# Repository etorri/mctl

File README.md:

# Objective

The purpose of this pile of rubbish is to build a controller between
Raspberry Pi UART (or SPI) and Pololu 708 (Dual VNH2SP30 Motor Driver
Carrier MD03A) with two DC gear motors (FIT0277).

The controller is based on msp430G2553 (20-pin) because I have several of them.
Besides that, it has nice peripherals to implement

- wall clock with timer A0 to measure time intervals (encoders)
- sufficiently fast two channel PWM (10-20KHz) with timers A1
- UART,SPI or I2C clock
- interrupts from the rotary encoders of the motors.
- just enough IO ports

The code is designed for this particular application. It may have
useful components and "Notes to Self" comments that somebody finds
useful.

# Control?

The Pi tells the controller to

- Initialize
- Break
- Prepare to run
- Run with given PWM values
- Error recovery
- Sleep

The controller reports back to Pi

- state of the controller
- position and speed (and current) of the two motors
- errors reported by the driver chip

# Pins wasted

The following pins of the msp430G2553 are misused for the purpose
(see the eagle files)

Left side, top to down

| Pin# | Port | Function | Description      |
|------+------+----------+------------------|
|    1 | DVCC | +3.3v    | Electrons exit   |
|    2 | P1.0 | IO       | out: L ENA       |
|    3 | P1.1 | UART RX  | data from Pi     |
|    4 | P1.2 | UART TX  | data to Pi       |
|    5 | P1.3 | IO       | in : L DIAG      |
|    6 | P1.4 | IO       | in : L Encoder B |
|    7 | P1.5 | IO       | in : L Encoder A |
|    8 | P2.0 | IO       | out: L INB       |
|    9 | P2.1 | TA1.1    | out: L PWM       |
|   10 | P2.2 | IO       | out: L INA       |

Right Side, top to down

| Pin# | Port | Function | Description       |
|------+------+----------+-------------------|
|   20 | DVSS | +0v      | Electrons enter   |
|   19 | P2.6 | IO       | out: R ENA        |
|   18 | P2.7 | IO       | in : R DIAG       |
|   17 | x    | TEST     | Programmer        |
|   16 | x    | RESET    | Programmer        |
|   15 | P1.7 | IO       | in :  R Encoder B |
|   14 | P1.6 | IO       | in :  R Encoder A |
|   13 | P2.5 | IO       | out: R INB        |
|   12 | P2.4 | TA1.2    | out: R PWM        |
|   11 | P2.3 | IO       | out: R INA        |

The motor driver also provides two Current Sense (CS) analog outputs
that tell how many amps go through a motor.

# CPU settings

Low power operation (at which the msp430 is also good at) is not
within the scope. It runs full speed 16MHz from the DCO oscillator.

# Motor control signals to the driver

The controller will handle the confusion that left motor will turn
Clockwise (CW) and right CounterClockWise (CCW) when going forward. 
The Power settings received from the Pi are signed integers bounded
by the timer A1 TA1CCR0 count (PWM frequency).
Negative number means going backwards and positive forwards.

Three states of INA and INB motor driver pins are used 

| State         | L INA | L INB | R INA | R INB |
|---------------|-------|-------|-------|-------|
| Power(x) >= 0 |     1 |     0 |     0 |     1 |
| Power(x) < 0  |     0 |     1 |     1 |     0 |
| Braking       |     0 |     0 |     0 |     0 |

Braking state means shorting both motors to ground. With the 51:1 gears
this shouldn't really be necessary.

The PWM has 10KHz frequency and motor driver documentation says max 20KHz.
DCO clock 16MHZ with

The driver operates at 5v and high level signal is 3.27v which is
uncomfortably close to the 3.3v of msp430 so level converters are needed.

The INA, INB pins in MSP need to be in the same port to be able to change
them simultaneously. Otherwise the motor might be in braking mode for
a short period. Documentation mentions 

Example:

~~~~
#define LINA BIT4 
#define LINB BIT3
P2OUT = (P2OUT&~LINB)|LINA; // Left motor forward in one op
P2OUT = (P2OUT&~LINA)|LINB; // Left motor backward
P2OUT &= ~(LINA|LINB);      // Left Brake
~~~~

# Encoder signals from the motors

*Speculation based on the vague docs, need to be verified with the hardware*

Hall effect quadrature encoder will give 13 interrupts per 
one motor rotation on the A input. The gearbox is 51:1 which makes it
663 interrupts per one rotation of the wheel.

At 16MHz it seems that by initial measurements
this MSP430 chip can handle 160K interrupts per second 
or 80K interrupts/s per wheel with highly unoptimized C code ISRs.
So the ISR is bounded with wheel speeds of 120r/s. The motor+gear documentation
mentions ~3 r/s for top speed which makes me believe this should not be a problem.

The accuracy looks pretty good when measured with the 2MHz wall clock
timer implemented with T0. Connecting the PWM output to encoder A input
gives variation of one step (0.5 microseconds).

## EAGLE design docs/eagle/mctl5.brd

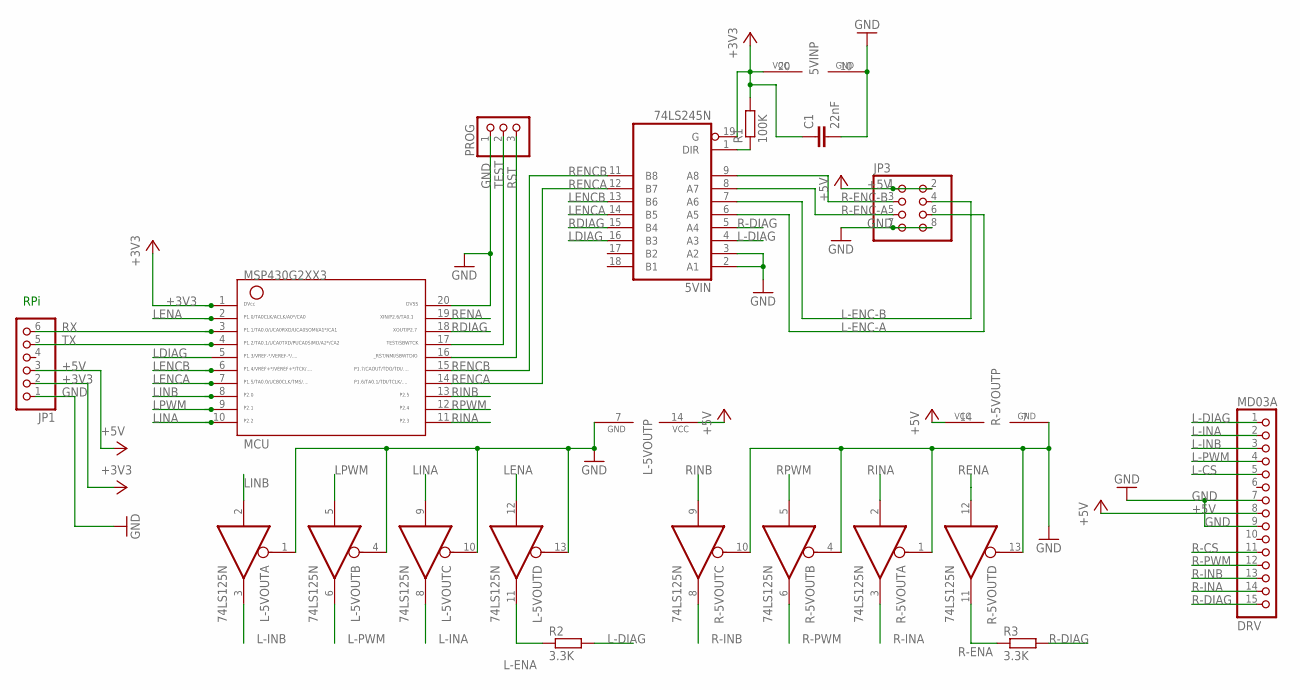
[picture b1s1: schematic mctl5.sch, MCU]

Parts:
5VIN: 74LS245N; DIL20
C1: 22nF; C025-024X044
JP1: PINHD-1X6; 1X06
JP3: PINHD-2X4; 2X04
L-5VOUT: 74LS125N; DIL14
MCU: G2XX3---N20; N20
MD03A: DRV; 1X15-CB
PROG: PINHD-1X3; 1X03
R1: 100K; 0204/7
R2, R3: 3.3K; 0204/7
R-5VOUT: 74LS125N; DIL14

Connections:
+3V3: 5VIN.19 (G), 5VIN.20 (VCC), C1.1, JP1.2, MCU.1, R1.2
+5V: JP1.3, JP3.1, JP3.2, L-5VOUT.14 (VCC), MD03A.8, R-5VOUT.14 (VCC)
GND: 5VIN.2 (A1), 5VIN.3 (A2), 5VIN.10 (GND), C1.2, JP1.1, JP3.7, JP3.8, L-5VOUT.1 (OE), L-5VOUT.4 (OE), L-5VOUT.7 (GND), L-5VOUT.10 (OE), L-5VOUT.13 (OE), MCU.20, MD03A.7, MD03A.9, PROG.1, R-5VOUT.1 (OE), R-5VOUT.4 (OE), R-5VOUT.7 (GND), R-5VOUT.10 (OE), R-5VOUT.13 (OE)
L-CS: MD03A.5
L-DIAG: 5VIN.4 (A3), MD03A.1, R2.2
L-ENA: L-5VOUT.11 (O), R2.1
L-ENC-A: 5VIN.6 (A5), JP3.6
L-ENC-B: 5VIN.7 (A6), JP3.4
L-INA: L-5VOUT.8 (O), MD03A.2
L-INB: L-5VOUT.3 (O), MD03A.3
L-PWM: L-5VOUT.6 (O), MD03A.4
LDIAG: 5VIN.16 (B3), MCU.5
LENA: L-5VOUT.12 (I), MCU.2
LENCA: 5VIN.14 (B5), MCU.7
LENCB: 5VIN.13 (B6), MCU.6
LINA: L-5VOUT.9 (I), MCU.10
LINB: L-5VOUT.2 (I), MCU.8
LPWM: L-5VOUT.5 (I), MCU.9
unnamed: 5VIN.1 (DIR), R1.1
R-CS: MD03A.11
R-DIAG: 5VIN.5 (A4), MD03A.15, R3.2
R-ENA: R3.1, R-5VOUT.11 (O)
R-ENC-A: 5VIN.8 (A7), JP3.5
R-ENC-B: 5VIN.9 (A8), JP3.3
R-INA: MD03A.14, R-5VOUT.3 (O)
R-INB: MD03A.13, R-5VOUT.8 (O)
R-PWM: MD03A.12, R-5VOUT.6 (O)
RDIAG: 5VIN.15 (B4), MCU.18
RENA: MCU.19, R-5VOUT.12 (I)
RENCA: 5VIN.12 (B7), MCU.14
RENCB: 5VIN.11 (B8), MCU.15
RINA: MCU.11, R-5VOUT.2 (I)
RINB: MCU.13, R-5VOUT.9 (I)
RPWM: MCU.12, R-5VOUT.5 (I)
RST: MCU.16, PROG.3
RX: JP1.6, MCU.3
TEST: MCU.17, PROG.2
TX: JP1.5, MCU.4

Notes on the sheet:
RPi

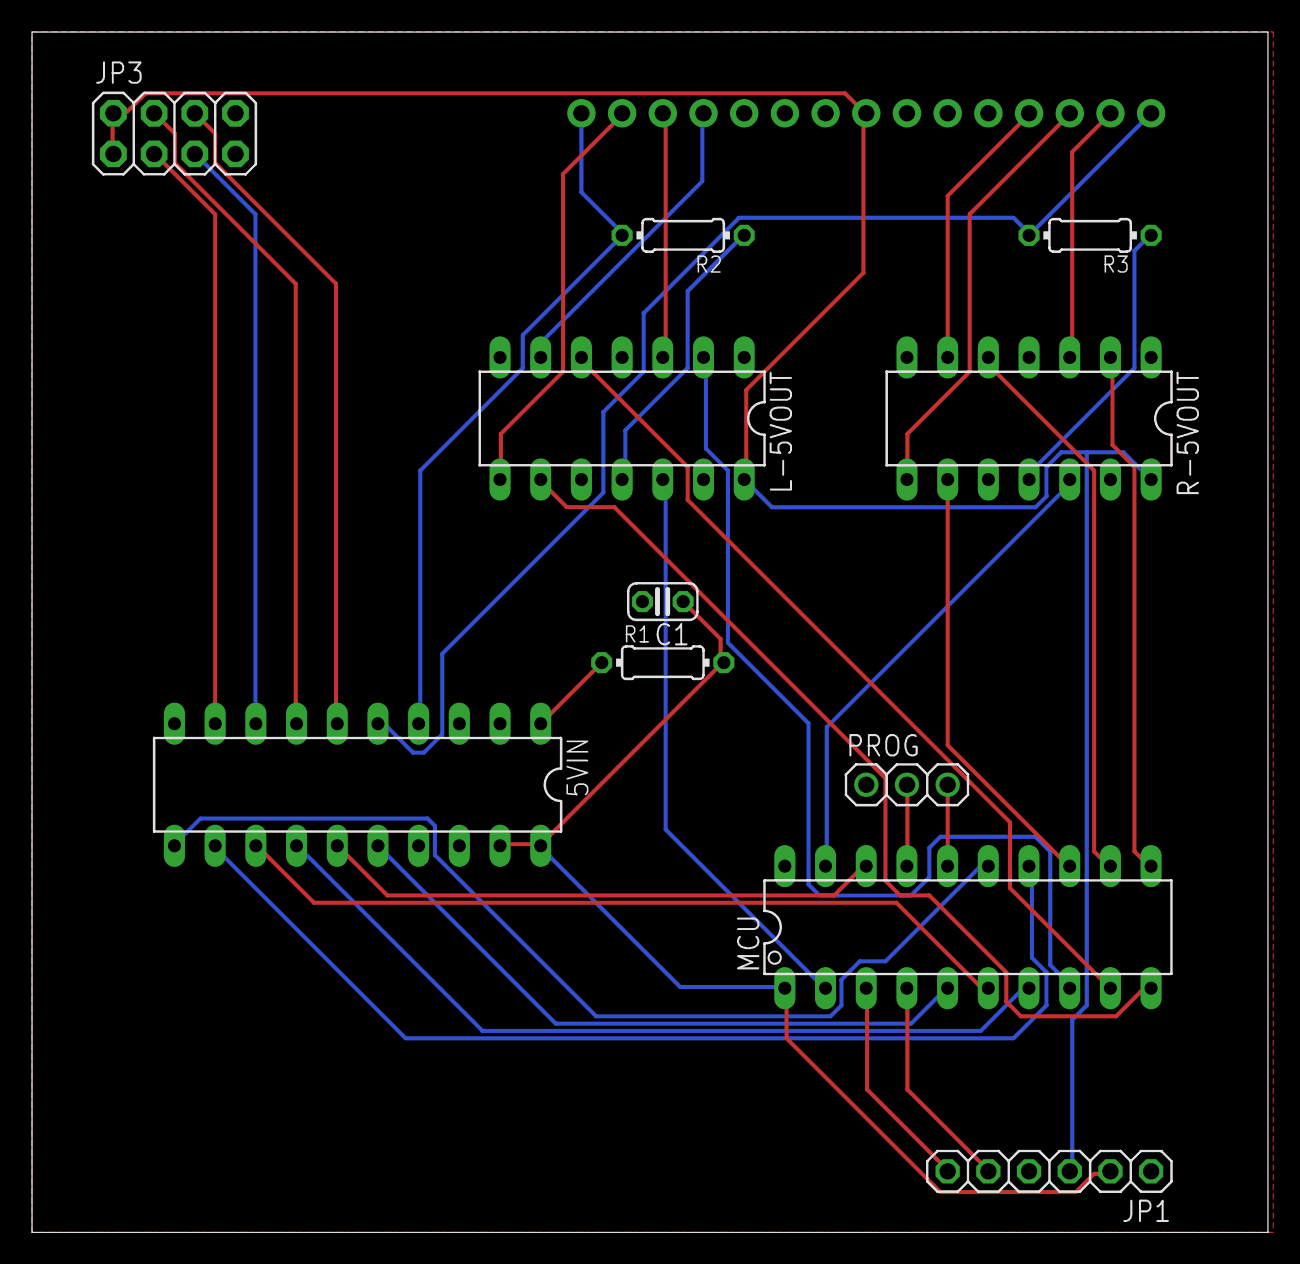
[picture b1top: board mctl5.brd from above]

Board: 2 copper layers, 77.1 x 74.9 mm, 12 parts (0 on the bottom side), 36 nets.

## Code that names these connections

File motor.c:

#include <msp430g2553.h>
#include <inttypes.h>
#include <stdlib.h>
#include "motor.h"
#include "pwm.h"
#include "clock.h"
#include "protocols.h"

// Motor control ports
// left INA port 2.0
#define LINA BIT0
// left INB port 2.2
#define LINB BIT2
// left DIAG port 2.6
#define LDIAG BIT6
// right INA port 2.3
#define RINA BIT3
// right INB port 2.5
#define RINB BIT5
// right DIAG port 2.7
#define RDIAG BIT7

// Encoder pins at port 1
#define LENCA BIT5
#define LENCB BIT4
#define RENCA BIT6
#define RENCB BIT7

// communication to/from the motor
motor_in m_in;
motor_out m_out;

volatile uint8_t mmsg=0;

// internal motor control variables
static   int16_t left_power;  
static   int16_t right_power;
// timeout timer to detect broken communication with pi
static  uint32_t power_timer;

// forward definitions
static inline void motor_set_power(void);
static inline void motor_ready(void);



// ----------------------------------------------------------------------
// --- initialize encoder inputs
//
void encoder_init(void){
  // clear position counters
  m_out.l_pos = m_out.r_pos = 0;
  // configure encoder pins
  P1SEL &= ~(LENCA|LENCB|RENCA|RENCB); // as gpio
  P1DIR &= ~(LENCA|LENCB|RENCA|RENCB); // as inputs
  P1IE  |= (RENCA|LENCA);              // A pins as interrupts
  P1IES &=  ~(RENCA|LENCA);            // rising edge
  // configure DIAG pins
  P2SEL &= ~(LDIAG|RDIAG);             // as gpio
  P2DIR &= ~(LDIAG|RDIAG);             // as input
  P2IE  |= (LDIAG|RDIAG);              // enable interrupt
  P2IES |= (LDIAG|RDIAG);              // falling edge
  
}

// ----------------------------------------------------------------------
// --- prepare motor driver for the READY state (stopped, breaking)
//
static inline void
motor_ready(void){
  // set pwm to 0
  left_power=right_power=0;
  motor_set_power();
  // motor in breaking state
  P2OUT &= ~(LINA|LINB|RINA|RINB);
}


// ----------------------------------------------------------------------
// --- Initialize the motor subsystem - called by mctl.c
// 
void
motor_init(void) {
  // configure INA/INB pins
  P2SEL  &= ~(LINA|LINB|RINA|RINB); // as gpio
  P2DIR  |= (LINA|LINB|RINA|RINB);  // as outputs
  // P2SEL2 &= ~(LINA|LINB|RINA|RINB); 
  P2IE   &= ~(LINA|LINB|RINA|RINB); 
  // initialize variables
  m_out.state=MSTATE_READY;
  m_in.msg=0;
  // do what is needed to enter the READY state
  motor_ready();
  encoder_init();
  // start with READY state so reporting interval is longer
  report_interval=READY_REPORT_INTERVAL;
}



// ----------------------------------------------------------------------
// --- Set the power for left motor
//
static inline void
motor_set_left(int power) {
  int8_t sgn;
  sgn= (power>=0);
  power=abs(power);
  if(sgn) {
    // power is positive => CW
    P2OUT = (P2OUT|LINA)&(~LINB);
  }else{
    // power is negative => CCW
    P2OUT = (P2OUT|LINB)&(~LINA);
  }
  pwm_l_set(power);
}


// ----------------------------------------------------------------------
// --- Set the power for right motor
//
static inline void
motor_set_right(int power) {
  int8_t sgn;
  sgn= (power>=0);
  power=abs(power);
  // set direction based on the sign of the power setting
  if(sgn) {
    P2OUT = (P2OUT|RINA)&(~RINB);
  }else{
    P2OUT = (P2OUT|RINB)&(~RINA);
  }
  // call helper to set the PWM
  pwm_r_set(power);
}


// ----------------------------------------------------------------------
// --- Set the power for both motors
//


static inline void
motor_set_power(void){
  motor_set_right(right_power);
  motor_set_left(left_power);
}



// ----------------------------------------------------------------------
// --- state machine to handle messages (in mmsg variable)
//
// the mmsg is set by protocols.c:input_scanner and any kind of failure
// detection mechanism. There is a risk for timing conflicts


void motor_step(void) {
  switch(m_out.state){
  case MSTATE_READY:
    // inputs
    if(mmsg&MMSG_FAIL){
      motor_ready();
      m_out.state=MSTATE_FAIL;
      report_interval=READY_REPORT_INTERVAL;
    } else if(mmsg&MMSG_POWER) {
      left_power=m_in.l_pwr;
      right_power=m_in.r_pwr;
      motor_set_power();
      set_timer(&power_timer);
      m_out.state=MSTATE_RUN;
      report_interval=RUN_REPORT_INTERVAL;
    }
    // clear inputs
    mmsg=0;
    break;
	  
  case MSTATE_RUN:
    // if Pi is not talking frequently enough (dead?) stop everything
    // and do not keep driving towards the cliff
    if(interval_elapsed(&power_timer,MAX_POWER_SETTING_INTERVAL)){
      mmsg=MMSG_FAIL;
    }
    // inputs
    if(mmsg&MMSG_FAIL) {
      motor_ready();
      report_interval=READY_REPORT_INTERVAL;
      m_out.state=MSTATE_FAIL;
      mmsg=0;
    } else if(mmsg&MMSG_POWER) {
      set_timer(&power_timer);
      left_power=m_in.l_pwr;
      right_power=m_in.r_pwr;
      motor_set_left(left_power);
      motor_set_right(right_power);
      m_out.state=MSTATE_RUN;
    } else if(mmsg&MMSG_STOP) {
      motor_ready();
      m_out.state=MSTATE_READY;
      report_interval=READY_REPORT_INTERVAL;
    }
    // clear inputs
    mmsg=0;
    break;

  case MSTATE_FAIL:
    // inputs
    if(mmsg&MMSG_CLEAR){
      m_out.state=MSTATE_READY;
      report_interval=READY_REPORT_INTERVAL;
    }
    // clear inputs and keep steady 
    mmsg=0;
    motor_ready();
    break;
  }
}


// ----------------------------------------------------------------------
// --- Interrupt Service Routines for rotary encoders and driver failures
//


// Encoders at port 1
void __attribute__((interrupt (PORT1_VECTOR))) p1isr() {
  // Left encoder interrupt
  if(P1IFG & LENCA) {
    // If L-ENC-B also up then going forward
    if(P1IN & LENCB){
      m_out.l_pos++;
    }else{
      m_out.l_pos--;
    }
    // Clear LENCA interrupt
    P1IFG &= ~LENCA;
  }
  // Right encoder interrupt
  if(P1IFG & RENCA) {
    // In right motor R-ENC-A and R-ENC-B means backwards
    if(P1IN & RENCB){
      m_out.r_pos--;
    }else{
      m_out.r_pos++;
    }
    // Clear RENCA interrupt
    P1IFG &= ~RENCA;
  }
}

// Motor driver diagnostic inputs at port 2
void __attribute__((interrupt (PORT2_VECTOR))) p2isr() {
  // RDIAG went down = Right motor fail
  if(P2IFG & RDIAG){
    P2IFG &= ~RDIAG;
    mmsg|= MMSG_FAIL;
  }
  // L-DIAG (2.6) went down = Left motor fail
  if(P2IFG & LDIAG){
    P2IFG &= ~LDIAG;
    mmsg|= MMSG_FAIL;
  }
}

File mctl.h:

extern void motor_init(void);

// state of the motor state machine
extern uint8_t motor_state;

// bitfield of messages sent to the motor state machine
extern uint8_t motor_msg;

// power setting communicated through these
extern int left_power;
extern int right_power;

// Motor control ports
// left INA port 2.0
#define LINA BIT0
// left INB port 2.2
#define LINB BIT2
// left ENA port 1.0
#define LENA BIT0
// left DIAG port 1.3
#define LDIAG BIT3
// right INA port 2.3
#define RINA BIT3
// right INB port 2.5
#define RINB BIT5
// right ENA port 2.6
#define RENA BIT6
// right DIAG port 2.7
#define RDIAG BIT7

// Motor states
#define MSTATE_READY    1
#define MSTATE_RUN      2
#define MSTATE_WDOG     3
#define MSTATE_FAIL     4

// Motor messages
#define MMSG_POWER      1
#define MMSG_STOP       2
#define MMSG_FAIL       4
#define MMSG_CLEAR      8
#define MMSG_TIMEOUT   16

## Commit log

2016-02-07 Initial confusing pile of components
2016-02-07 Initial readme
2016-02-07 Github tables formatting WTF
2016-02-07 Github tables formatting WTF adjustment2
2016-02-10 New modules: Encoder interrupt handlers, wall clock Changed: pwm now with timer 1 only, documentation with changed pin organization
2016-02-10 table formatting
2016-02-14 Add: Motor control (direction, power), buffered uart, chip documents
2016-02-14 first plan for the electronics
2016-02-19 First test version of motor driver controller
    Additional feature: ENAble signal for both motors which pulls the DIAG/ENA line to +5V with 3.3K resistor.
    This moves the motor driver to low-power state when not driving. It also keeps the motor driver disabled
    at start until the controller decides to start it.
2016-02-25 The main program will be split to testing versions
2016-03-09 Moving to separate uart input, output handling
2016-03-15 daily sync
2016-03-31 Packet length problems: MSP aliasing and last-but-one error in counter
2016-05-04 removed test versions
2016-05-08 sync with repo
2017-06-08 Improved packet protocol that actually works
